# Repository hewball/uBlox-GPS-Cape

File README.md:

# uBlox-GPS-Cape
uBlox GPS Cape for using a Beaglebone as an NTP Stratum 1

More details on http://hewball.com.au

# License 
<br />This work is licensed under a <a rel="license" href="http://creativecommons.org/licenses/by-nc-sa/4.0/">Creative Commons Attribution-NonCommercial-ShareAlike 4.0 International License</a>.

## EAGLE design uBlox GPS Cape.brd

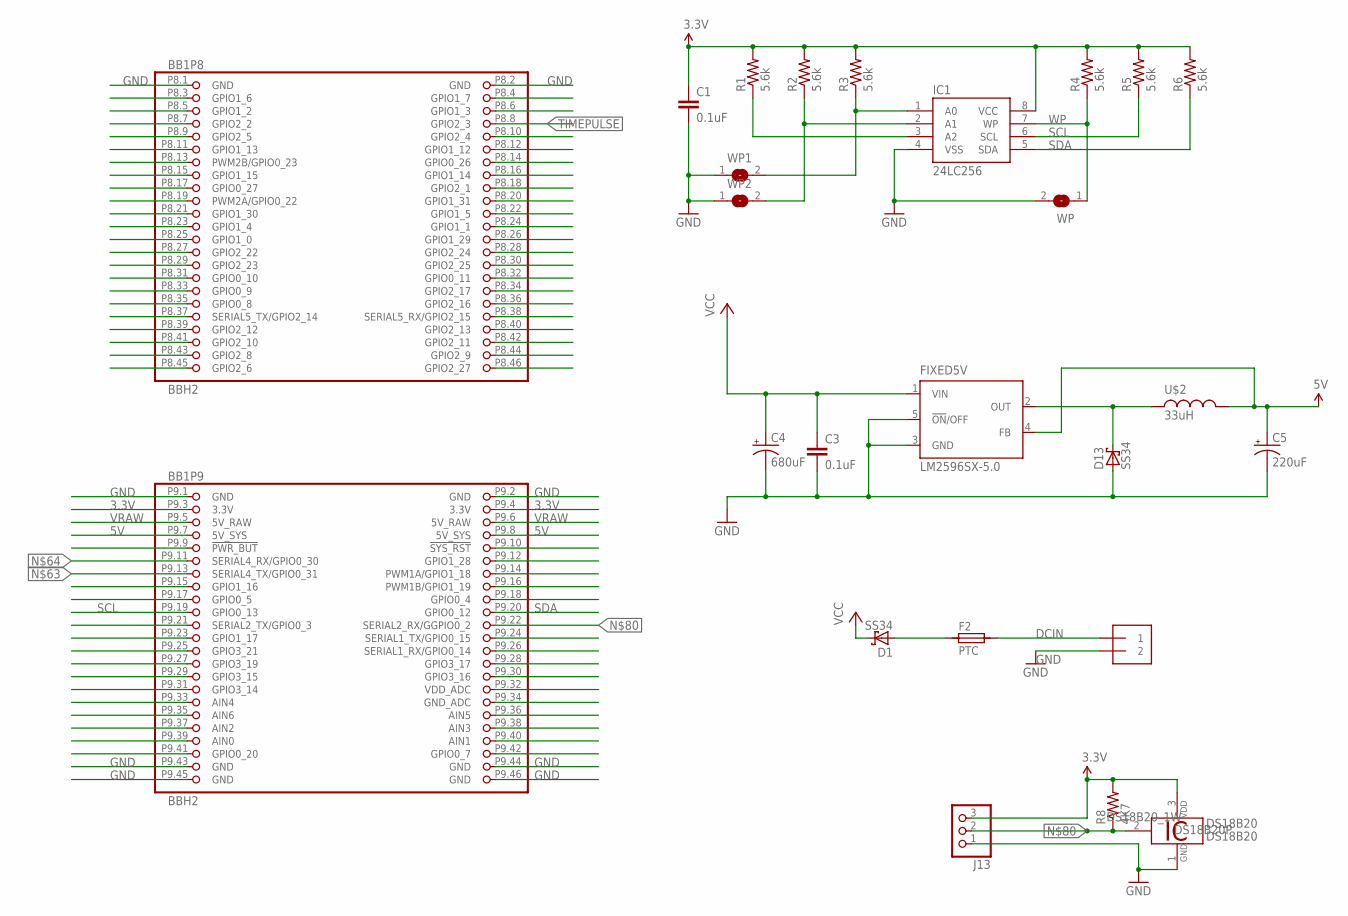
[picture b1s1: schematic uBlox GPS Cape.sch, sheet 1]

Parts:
BB1: BBH2; BB_CAPE_TOP
C1, C3: 0.1uF; 0603-CAP
C4: 680uF; PANASONIC_H13
C5: 220uF; 153CLV-0810
D1, D13: SS34; SMC
DS18B20: DS18B20; TO92-
F2: PTC; 2920
FIXED5V: LM2596SX-5.0; TO263-5
IC1: 24LC256; SO08
J1: 1X2-3.5MM
J13: HEADER_1X3
R1, R2, R3, R4, R5, R6: 5.6k; 0603-RES
R8: 4K7; 0805
U$2: 33uH; MSS1260
WP, WP1, WP2: SJH; SJ

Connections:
3.3V: BB1.P9.3 (3.3V), BB1.P9.4 (3.3V), C1.1, DS18B20.3 (VDD), IC1.8 (VCC), J13.3, R1.2, R2.2, R3.2, R4.2, R5.2, R6.2, R8.2; also elsewhere on the board
5V: BB1.P9.7 (5V_SYS), BB1.P9.8 (5V_SYS)
DCIN: F2.2, J1.1
GND: BB1.P8.1 (GND), BB1.P8.2 (GND), BB1.P9.1 (GND), BB1.P9.2 (GND), BB1.P9.43 (GND), BB1.P9.44 (GND), BB1.P9.45 (GND), BB1.P9.46 (GND), C1.2, C3.2, C4.-, C5.-, D13.A, DS18B20.1 (GND), FIXED5V.3 (GND), FIXED5V.5 (!ON!/OFF), IC1.4 (VSS), J1.2, J13.1, WP.2, WP1.1, WP2.1; also elsewhere on the board
unnamed 60: BB1.P9.13 (SERIAL4_TX/GPIO0_31); also elsewhere on the board
unnamed 61: BB1.P9.11 (SERIAL4_RX/GPIO0_30); also elsewhere on the board
unnamed: BB1.P9.22 (SERIAL2_RX/GGPIO0_2), DS18B20.2 (1W), J13.2, R8.1
unnamed: D13.C, FIXED5V.2 (OUT), U$2.P$2
unnamed: D1.A, F2.1
unnamed: IC1.1 (A0), R3.1, WP1.2
unnamed: IC1.2 (A1), R2.1, WP2.2
unnamed: IC1.3 (A2), R1.1
SCL: BB1.P9.19 (GPIO0_13), IC1.6 (SCL), R5.1
SDA: BB1.P9.20 (GPIO0_12), IC1.5 (SDA), R6.1
TIMEPULSE: BB1.P8.8 (GPIO2_3); also elsewhere on the board
VCC: C3.1, C4.+, D1.C, FIXED5V.1 (VIN)
VRAW: BB1.P9.5 (5V_RAW), BB1.P9.6 (5V_RAW), C5.+, FIXED5V.4 (FB), U$2.P$1
WP: IC1.7 (WP), R4.1, WP.1

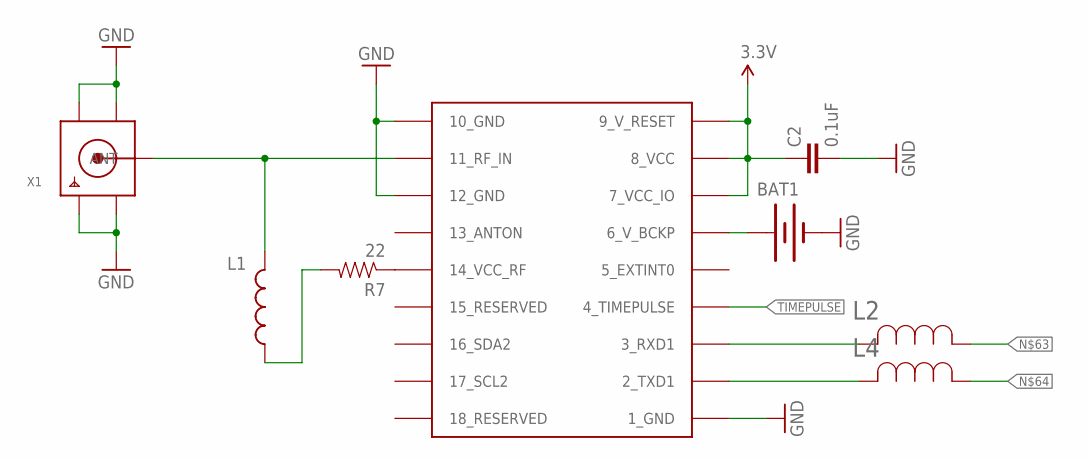
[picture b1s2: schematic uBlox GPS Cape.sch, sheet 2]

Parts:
BAT1: BATTERY12MM; BATTCON_12MM; MPN BK-890
C2: 0.1uF; 0603-CAP; MPN CC0805KRX7R9BB104
L1: INDUCTOR0603; 0603; MPN LBR2012T220K
L2, L4: BLM18HG102SN1D; IND_BLM18_0603; MPN BLM18HG102SN1D
R7: 22; 0603-RES; MPN RMCF0805JT22R0
U$1: UBLOX_MAX; MPN MAX-7Q
X1: SMACONNECTOR_EDGE_UFL; SMA_EDGELAUNCH_UFL

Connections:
3.3V: C2.1, U$1.7_VCC_IO, U$1.8_VCC, U$1.9_V_RESET; also elsewhere on the board
GND: BAT1.GND (-), C2.2, U$1.1_GND, U$1.10_GND, U$1.12_GND, X1.GND@1 (GND1), X1.GND@2 (GND2), X1.GND@3 (GND3), X1.GND@4 (GND4); also elsewhere on the board
unnamed 60: L2.1; also elsewhere on the board
unnamed 61: L4.1; also elsewhere on the board
unnamed: R7.1, U$1.14_VCC_RF
unnamed: L1.2, R7.2
unnamed: BAT1.PWR@1 (+), BAT1.VCC@1, U$1.6_V_BCKP
unnamed: L2.2, U$1.3_RXD1
unnamed: L4.2, U$1.2_TXD1
RF: L1.1, U$1.11_RF_IN, X1.P (ANT)
TIMEPULSE: U$1.4_TIMEPULSE; also elsewhere on the board

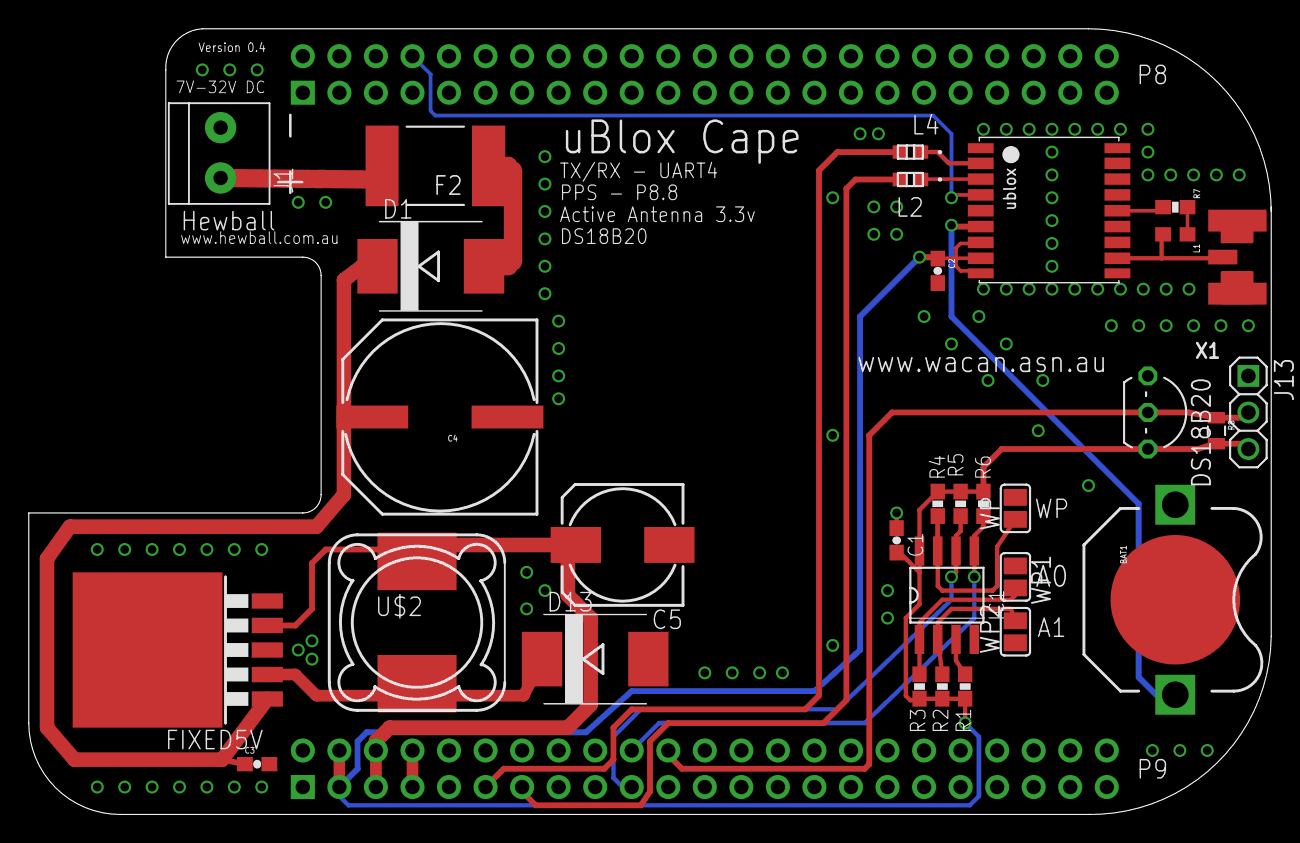
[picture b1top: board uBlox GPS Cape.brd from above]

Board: 2 copper layers, 86.4 x 54.6 mm, 32 parts (1 on the bottom side), 24 nets.

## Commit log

2016-06-29 Add files via upload
    Adding Schematic and Board designs

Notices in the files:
parts and their libraries:
SparkFun-Electromechanical: Licensing: Creative Commons ShareAlike 4.0 International - https://creativecommons.org/licenses/by-sa/4.0
SparkFun-Resistors: Licensing: CC v3.0 Share-Alike You are welcome to use this library for commercial purposes.
